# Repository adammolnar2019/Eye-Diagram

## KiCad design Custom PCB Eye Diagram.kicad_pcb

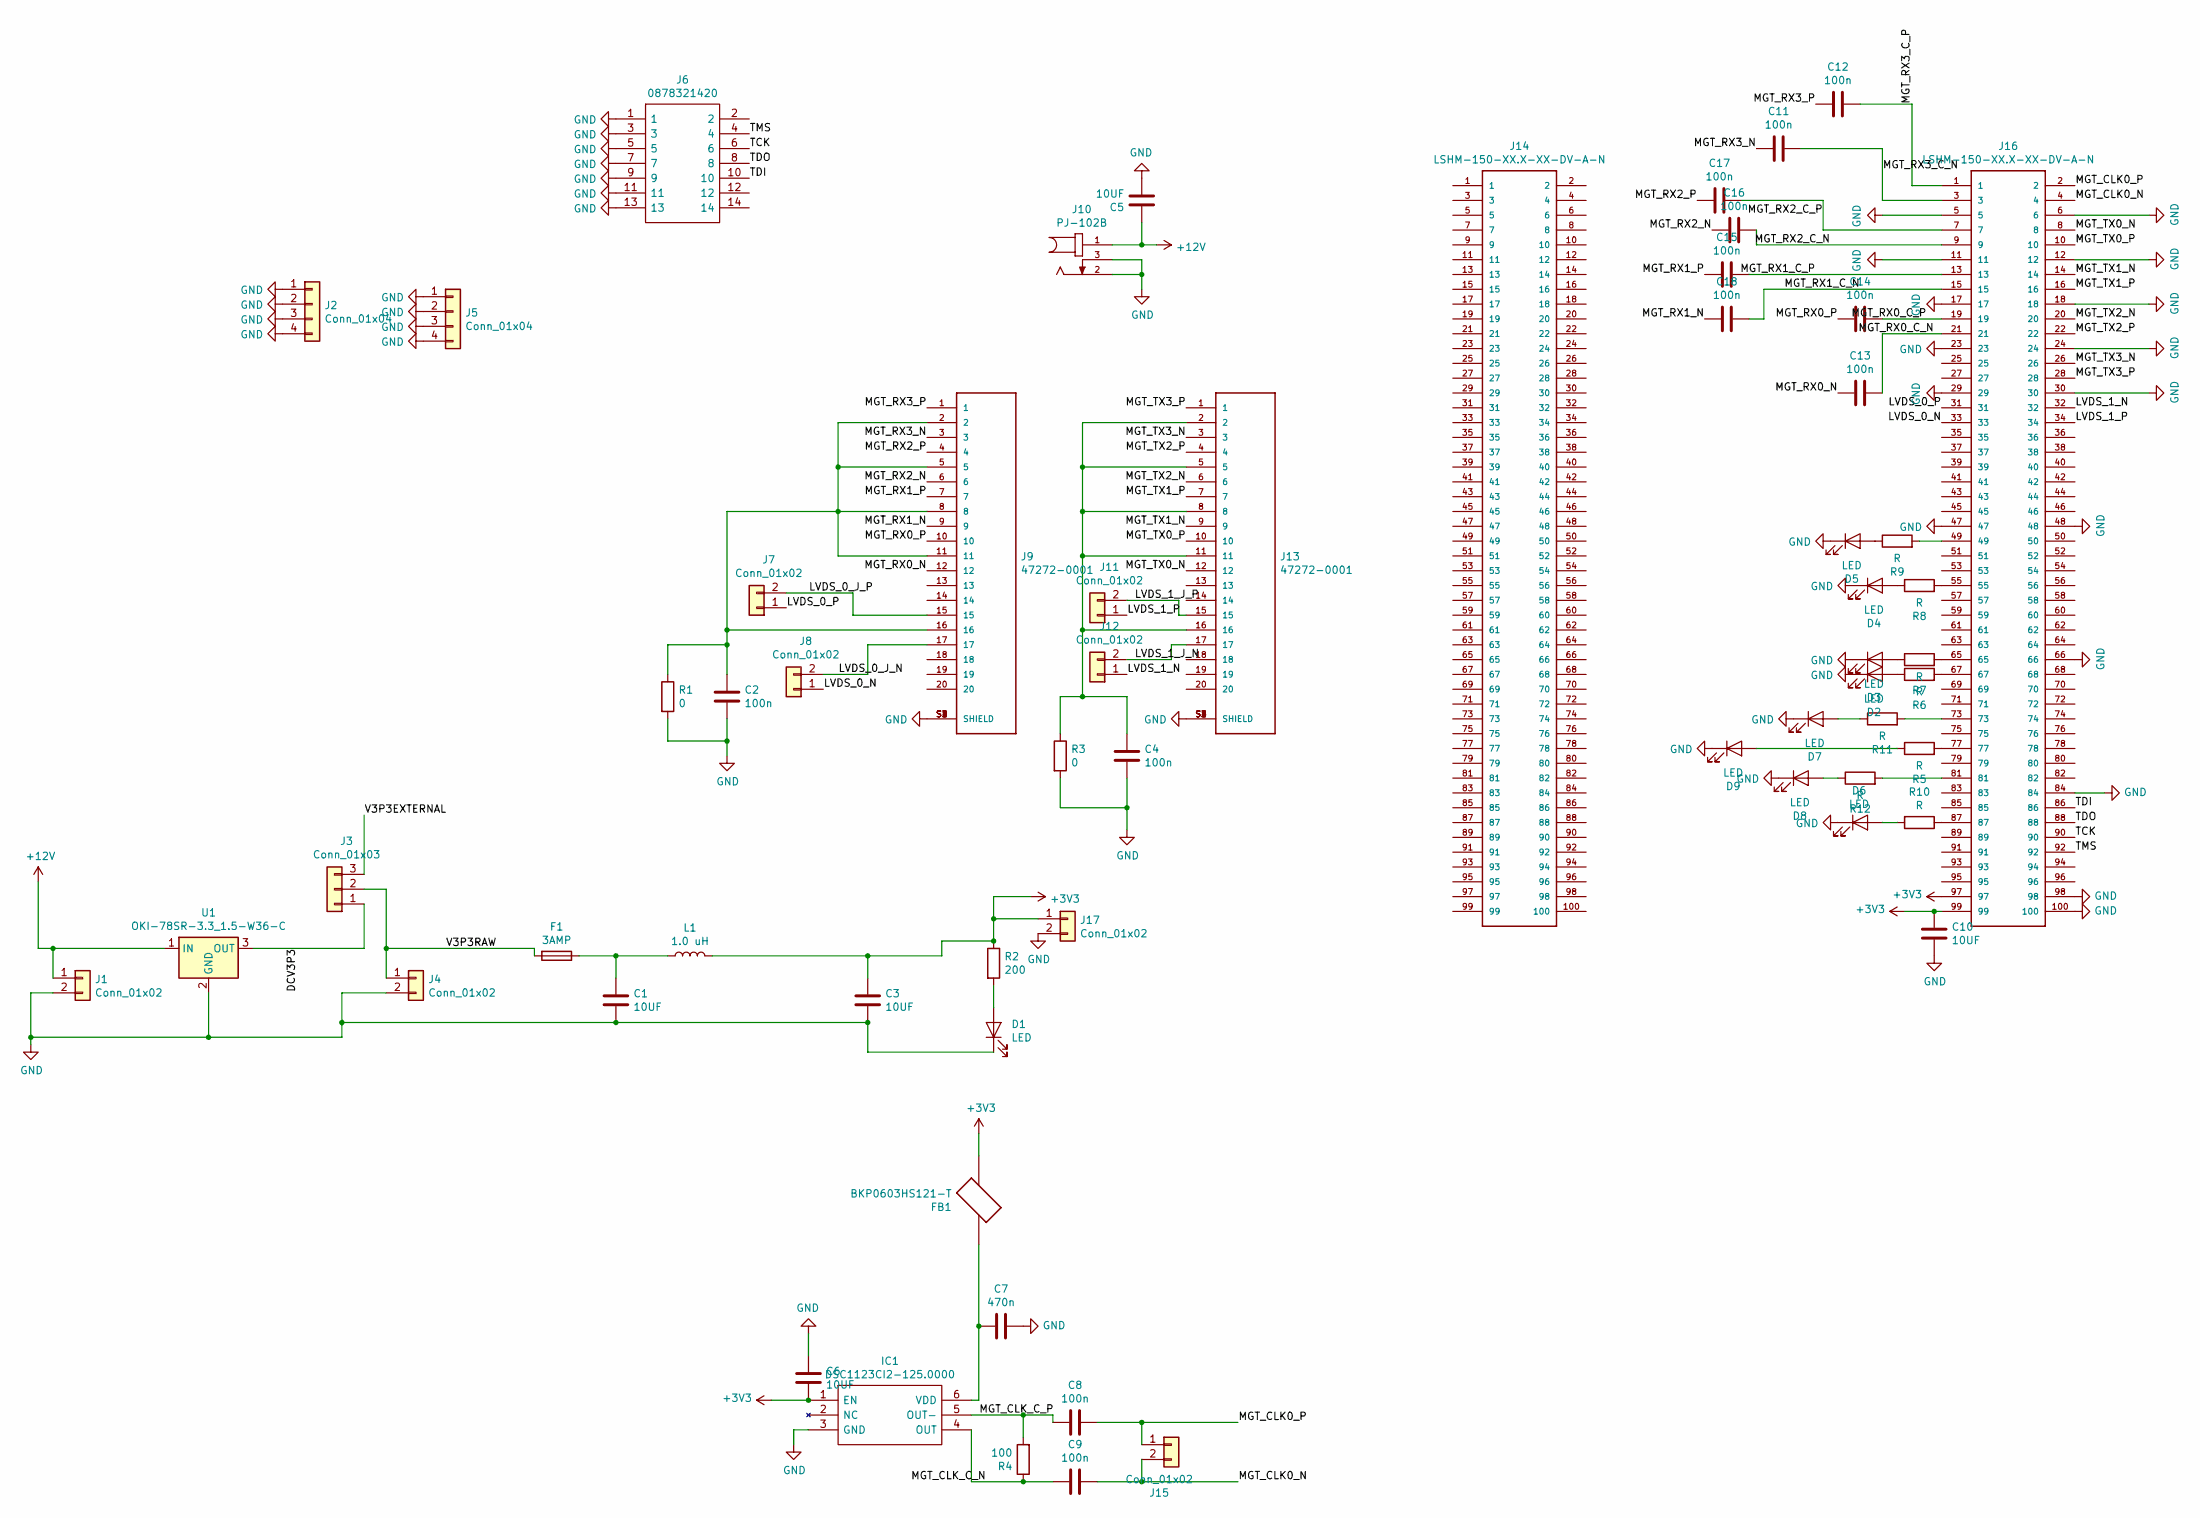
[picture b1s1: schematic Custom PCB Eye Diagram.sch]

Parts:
C1, C3, C5, C6, C10: 10UF; C_0805_2012Metric
C2, C4, C8, C9, C11, C12, C13, C14, C15, C16, C17, C18: 100n; C_0402_1005Metric
C7: 470n; C_0805_2012Metric
D1, D2, D3, D4, D5, D6, D7, D8, D9: LED; LED_0603_1608Metric
F1: 3AMP; Fuse_0603_1608Metric
FB1: BKP0603HS121-T; BEADC0603X33N
IC1: DSC1123CI2-125.0000; DSC1123CI21000000; Manufacturer_Part_Number DSC1123CI2-125.0000; Mouser Part Number 998-1123CI2-125.0000
J1, J4, J7, J8, J11, J12, J15, J17: Conn_01x02; PinHeader_1x02_P2.54mm_Vertical
J2, J5: Conn_01x04; PinHeader_1x04_P2.54mm_Vertical
J3: Conn_01x03; PinHeader_1x03_P2.54mm_Vertical
J6: 0878321420; 87832-1420_1; Manufacturer_Part_Number 0878321420; Mouser Part Number N/A
J9, J13: 47272-0001; MOLEX_47272-0001
J10: PJ-102B; CUI_PJ-102B
J14, J16: LSHM-150-XX.X-XX-DV-A-N
L1: 1.0 uH; L_0603_1608Metric
R1, R3: 0; R_0402_1005Metric
R2: 200; R_0603_1608Metric
R4: 100; R_0402_1005Metric
R5, R6, R7, R8, R9, R10, R11, R12: R; R_0402_1005Metric
U1: OKI-78SR-3.3_1.5-W36-C; Converter_DCDC_RECOM_R-78B-2.0_THT

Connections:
+3V3: C3.1, C6.2, C10.1, FB1.2, IC1.1 (EN), J16.97, J16.99, J17.1, L1.2, R2.1
+12V: C5.1, J1.1, J10.1, U1.1 (IN)
/DCV3P3: J3.1, U1.3 (OUT)
/LVDS_0_J_N: J8.2, J9.17
/LVDS_0_J_P: J7.2, J9.15
/LVDS_0_N: J8.1, J16.33
/LVDS_0_P: J7.1, J16.31
/LVDS_1_J_N: J12.2, J13.17
/LVDS_1_J_P: J11.2, J13.15
/LVDS_1_N: J12.1, J16.32
/LVDS_1_P: J11.1, J16.34
/MGT_CLK0_N: C9.1, J15.2, J16.4
/MGT_CLK0_P: C8.1, J15.1, J16.2
/MGT_CLK_C_N: C9.2, IC1.4 (OUT), R4.1
/MGT_CLK_C_P: C8.2, IC1.5 (OUT-), R4.2
/MGT_RX0_C_N: C13.1, J16.21
/MGT_RX0_C_P: C14.1, J16.19
/MGT_RX0_N: C13.2, J9.12
/MGT_RX0_P: C14.2, J9.10
/MGT_RX1_C_N: C18.1, J16.15
/MGT_RX1_C_P: C15.1, J16.13
/MGT_RX1_N: C18.2, J9.9
/MGT_RX1_P: C15.2, J9.7
/MGT_RX2_C_N: C16.1, J16.9
/MGT_RX2_C_P: C17.1, J16.7
/MGT_RX2_N: C16.2, J9.6
/MGT_RX2_P: C17.2, J9.4
/MGT_RX3_C_N: C11.2, J16.3
/MGT_RX3_C_P: C12.1, J16.1
/MGT_RX3_N: C11.1, J9.3
/MGT_RX3_P: C12.2, J9.1
/MGT_TX0_N: J13.12, J16.8
/MGT_TX0_P: J13.10, J16.10
/MGT_TX1_N: J13.9, J16.14
/MGT_TX1_P: J13.7, J16.16
/MGT_TX2_N: J13.6, J16.20
/MGT_TX2_P: J13.4, J16.22
/MGT_TX3_N: J13.3, J16.26
/MGT_TX3_P: J13.1, J16.28
/TCK: J6.6, J16.90
/TDI: J6.10, J16.86
/TDO: J6.8, J16.88
/TMS: J6.4, J16.92
/V3P3RAW: F1.2, J3.2, J4.1
GND: C1.2, C2.2, C3.2, C4.2, C5.2, C6.1, C7.1, C10.2, D1.1 (K), D2.1 (K), D3.1 (K), D4.1 (K), D5.1 (K), D6.1 (K), D7.1 (K), D8.1 (K), D9.1 (K), IC1.3 (GND), J1.2, J2.1, J2.2, J2.3, J2.4, J4.2, J5.1, J5.2, J5.3, J5.4, J6.1, J6.3, J6.5, J6.7, J6.9, J6.11, J6.13, J9.S1 (SHIELD), J9.S2 (SHIELD), J9.S3 (SHIELD), J9.S4 (SHIELD), J10.2, J10.3, J13.S1 (SHIELD), J13.S2 (SHIELD), J13.S3 (SHIELD), J13.S4 (SHIELD), J16.5, J16.6, J16.11, J16.12, J16.17, J16.18, J16.23, J16.24, J16.29, J16.30, J16.47, J16.48, J16.66, J16.84, J16.98, J16.100, J17.2, R1.2, R3.2, U1.2 (GND)
unnamed: C1.1, F1.1, L1.1
unnamed: C2.1, J9.2, J9.5, J9.8, J9.11, J9.16, R1.1
unnamed: C4.1, J13.2, J13.5, J13.8, J13.11, J13.16, R3.1
unnamed: C7.2, FB1.1, IC1.6 (VDD)
unnamed: D1.2 (A), R2.2
unnamed: D2.2 (A), R6.1
unnamed: D3.2 (A), R7.1
unnamed: D4.2 (A), R8.1
unnamed: D5.2 (A), R9.1
unnamed: D6.2 (A), R10.2
unnamed: D7.2 (A), R11.1
unnamed: D8.2 (A), R12.1
unnamed: D9.2 (A), R5.1
unnamed: J16.49, R9.2
unnamed: J16.55, R8.2
unnamed: J16.65, R7.2
unnamed: J16.67, R6.2
unnamed: J16.73, R11.2
unnamed: J16.77, R5.2
unnamed: J16.81, R12.2
unnamed: J16.87, R10.1

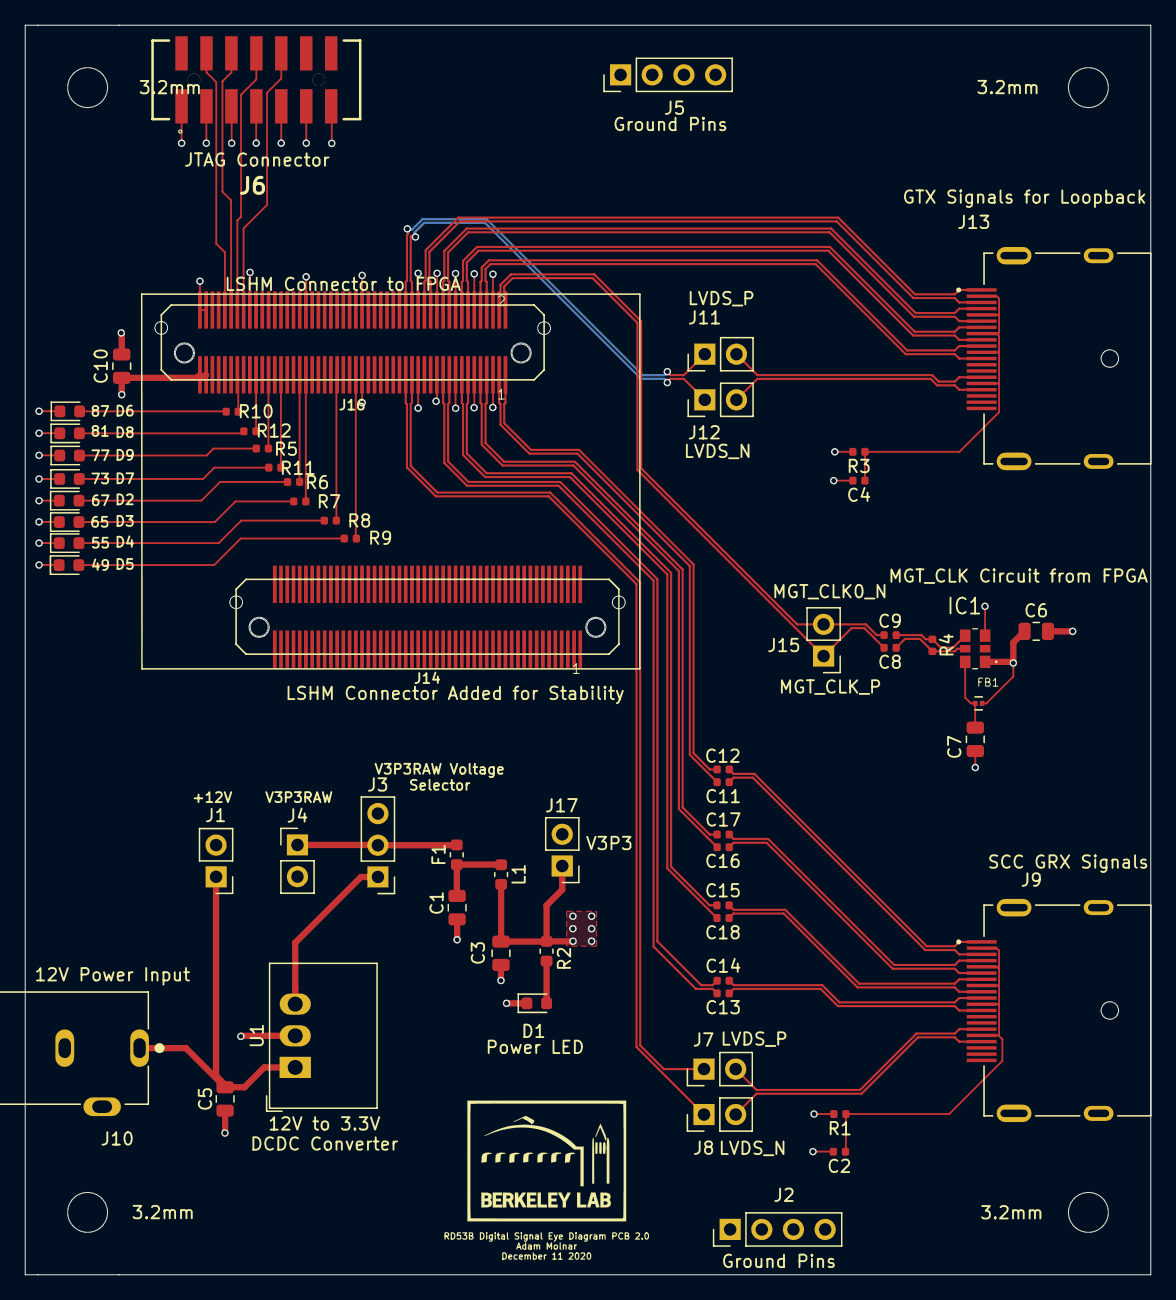
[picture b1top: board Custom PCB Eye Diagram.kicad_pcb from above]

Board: 4 copper layers, 90.3 x 100.2 mm, 65 parts (0 on the bottom side), 66 nets.

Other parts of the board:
3.2mm, 3.2mm , 3.2mm#2, 3.2mm#3: MountingHole_3.2mm_M3

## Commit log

2020-07-20 Added test LEDs for practicing FPGA programming
2020-07-22 Fixed test LED setup for FPGA programming practice
2020-07-28 Added the BOM to git
2020-08-24 Added LBNL logo, name, and changed VIN layer to V3P3 layer
2020-10-07 Another iteration of the PCB and made some updates to the BOM
2020-10-15 Changed the trace width and trace spacing to the proper values needed for impedance matching
2020-12-12 PCB 2.0
2021-01-07 Made changes to the LSHM footprints
2021-01-07 Further changes to LSHM connectors
2021-01-08 Moved silkscreen for C9 slightly
